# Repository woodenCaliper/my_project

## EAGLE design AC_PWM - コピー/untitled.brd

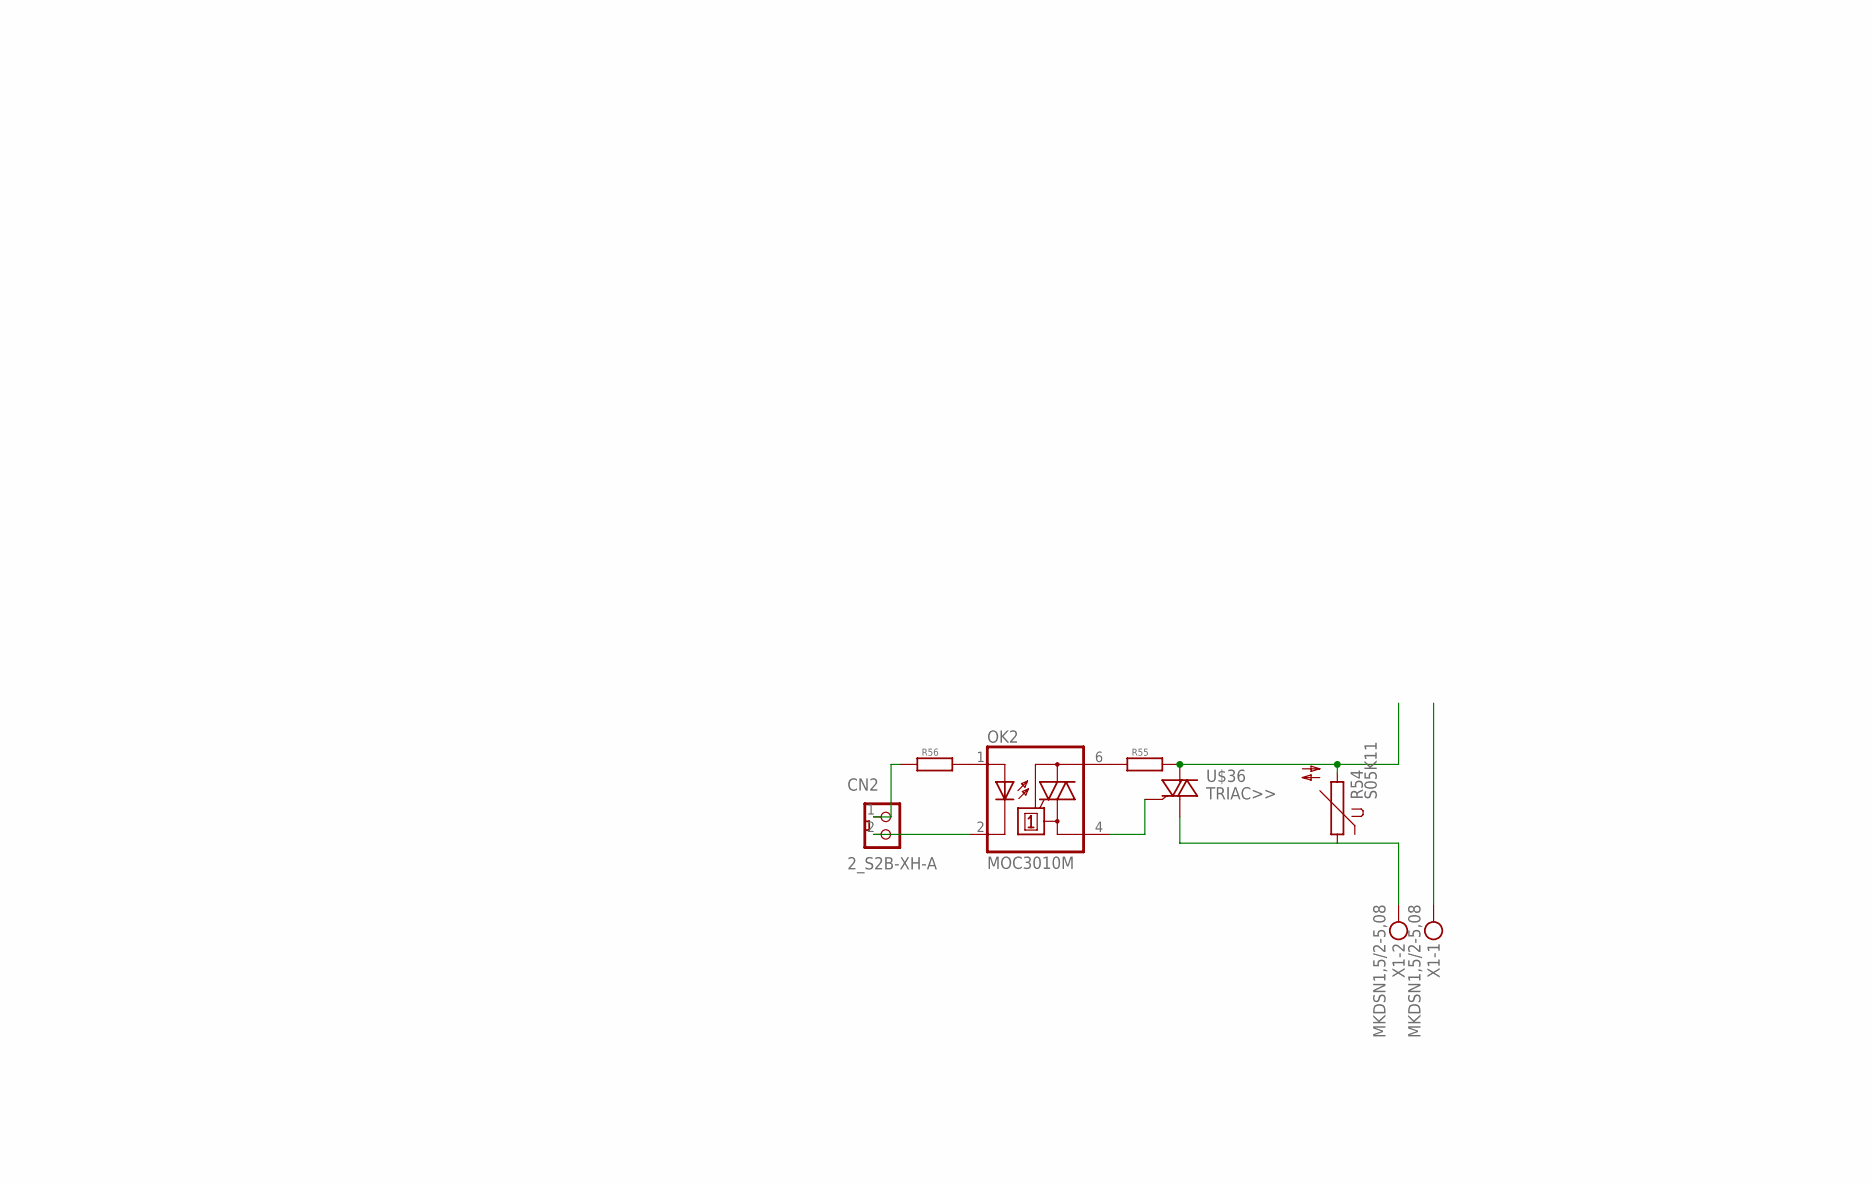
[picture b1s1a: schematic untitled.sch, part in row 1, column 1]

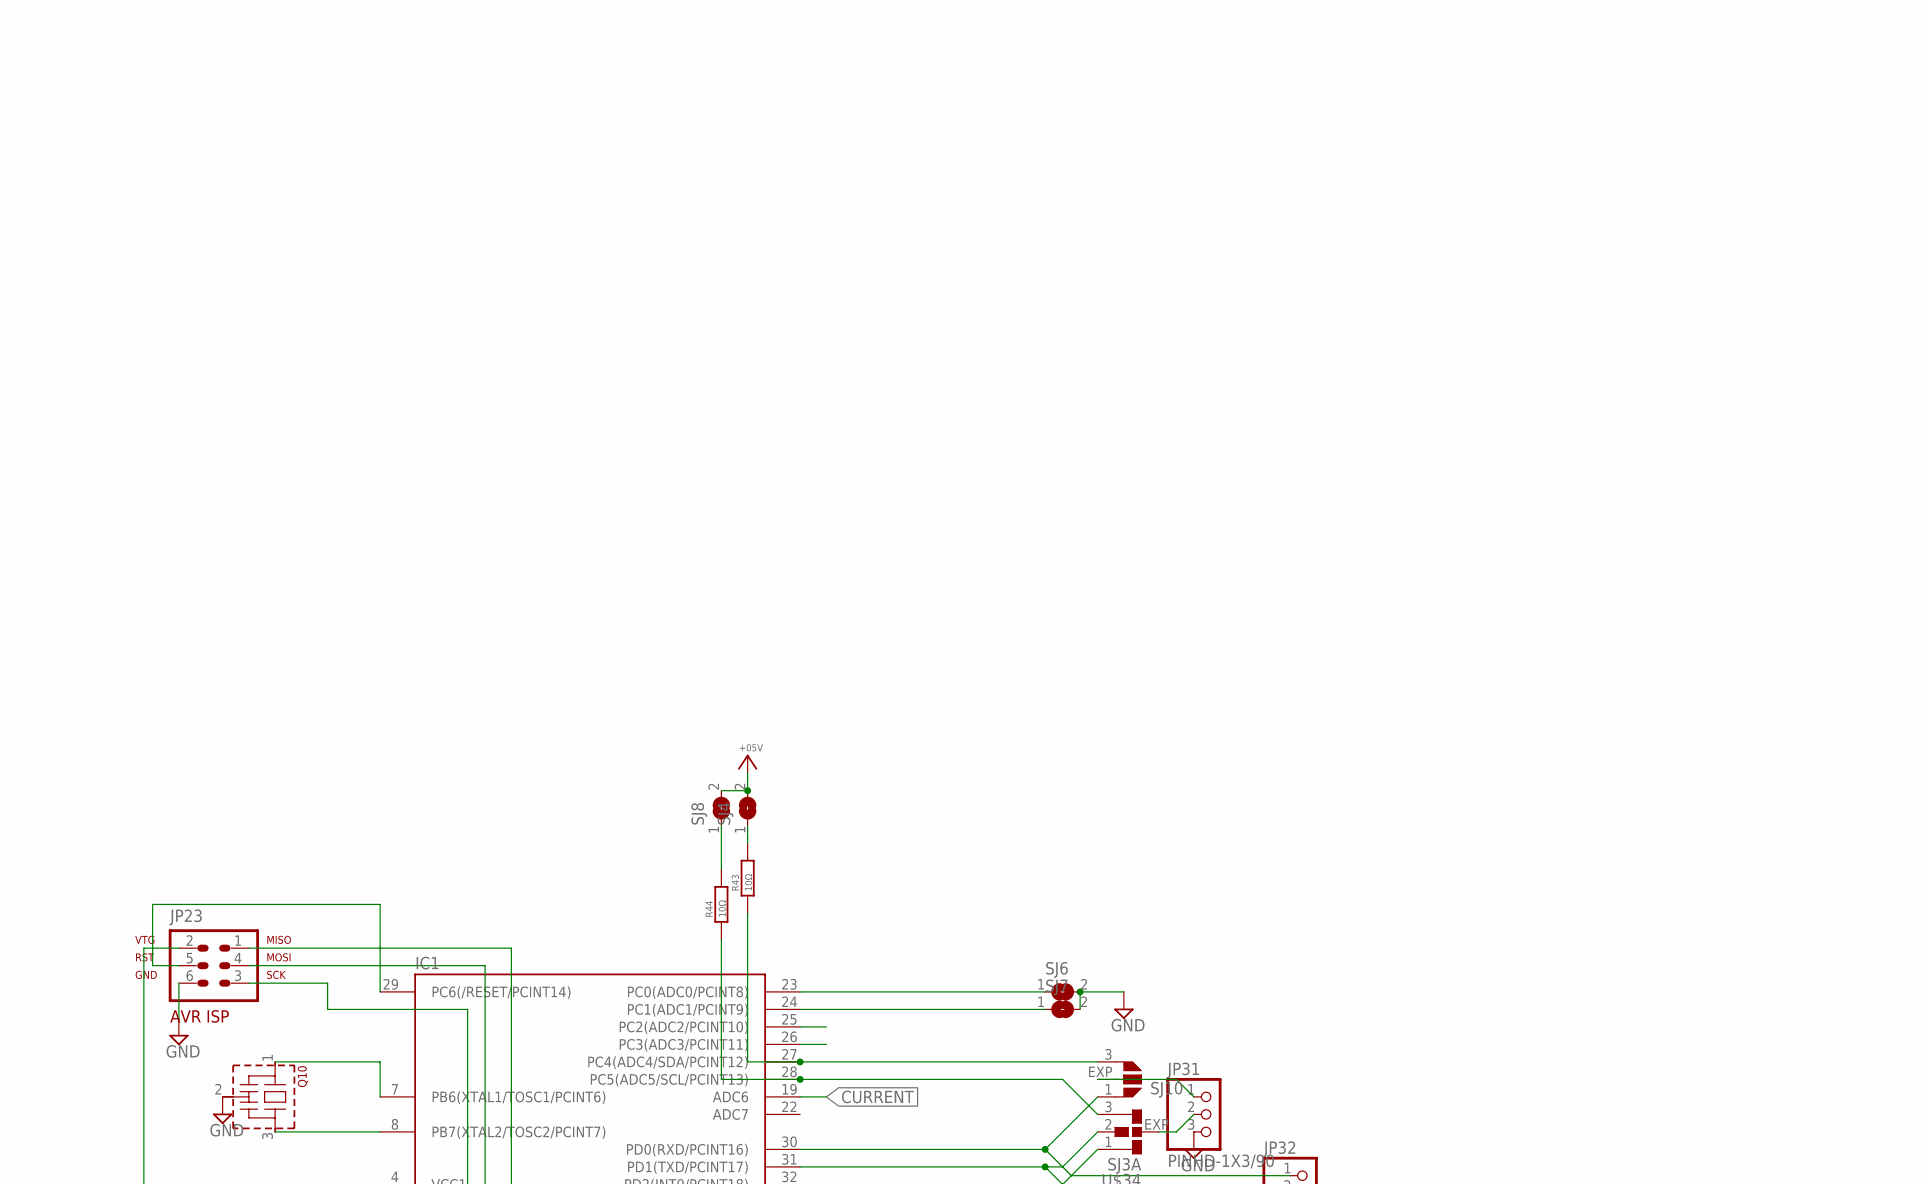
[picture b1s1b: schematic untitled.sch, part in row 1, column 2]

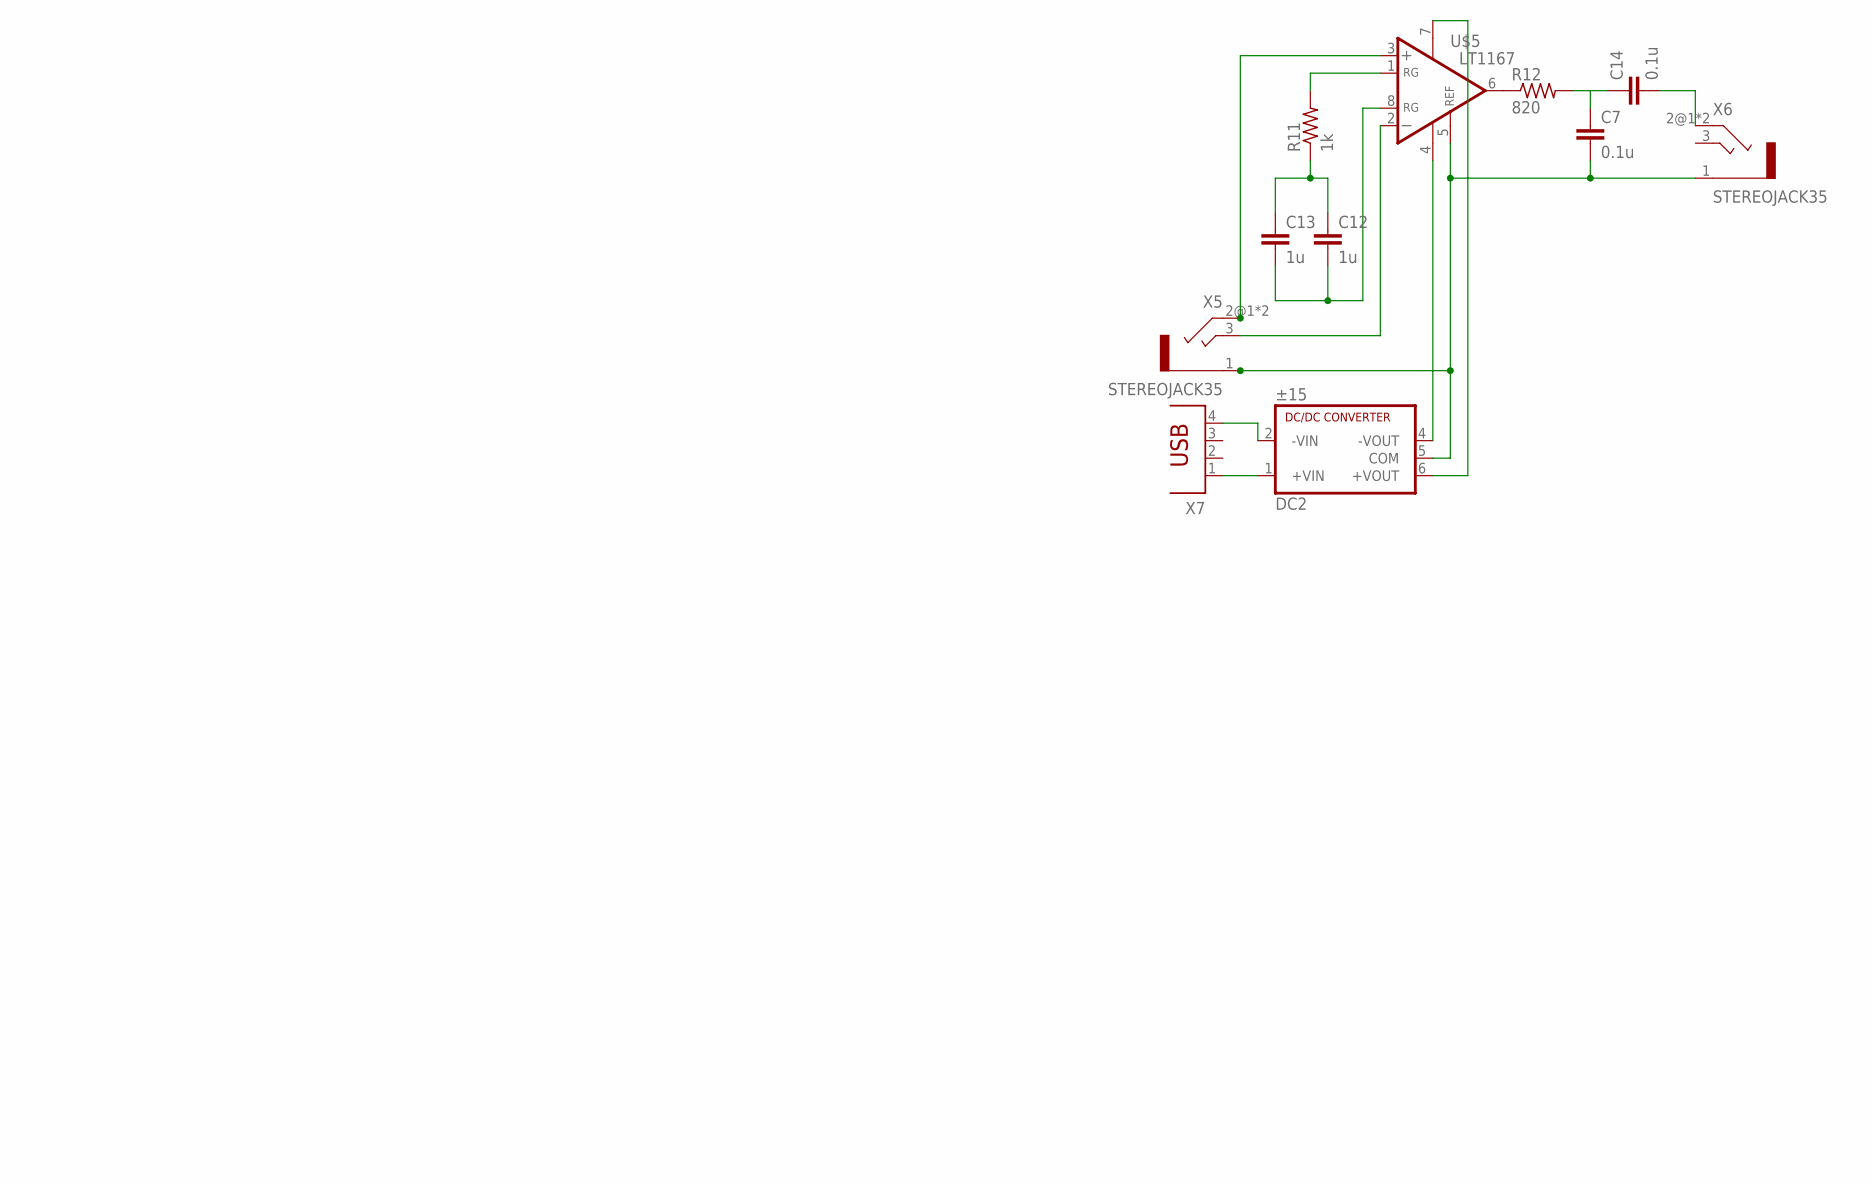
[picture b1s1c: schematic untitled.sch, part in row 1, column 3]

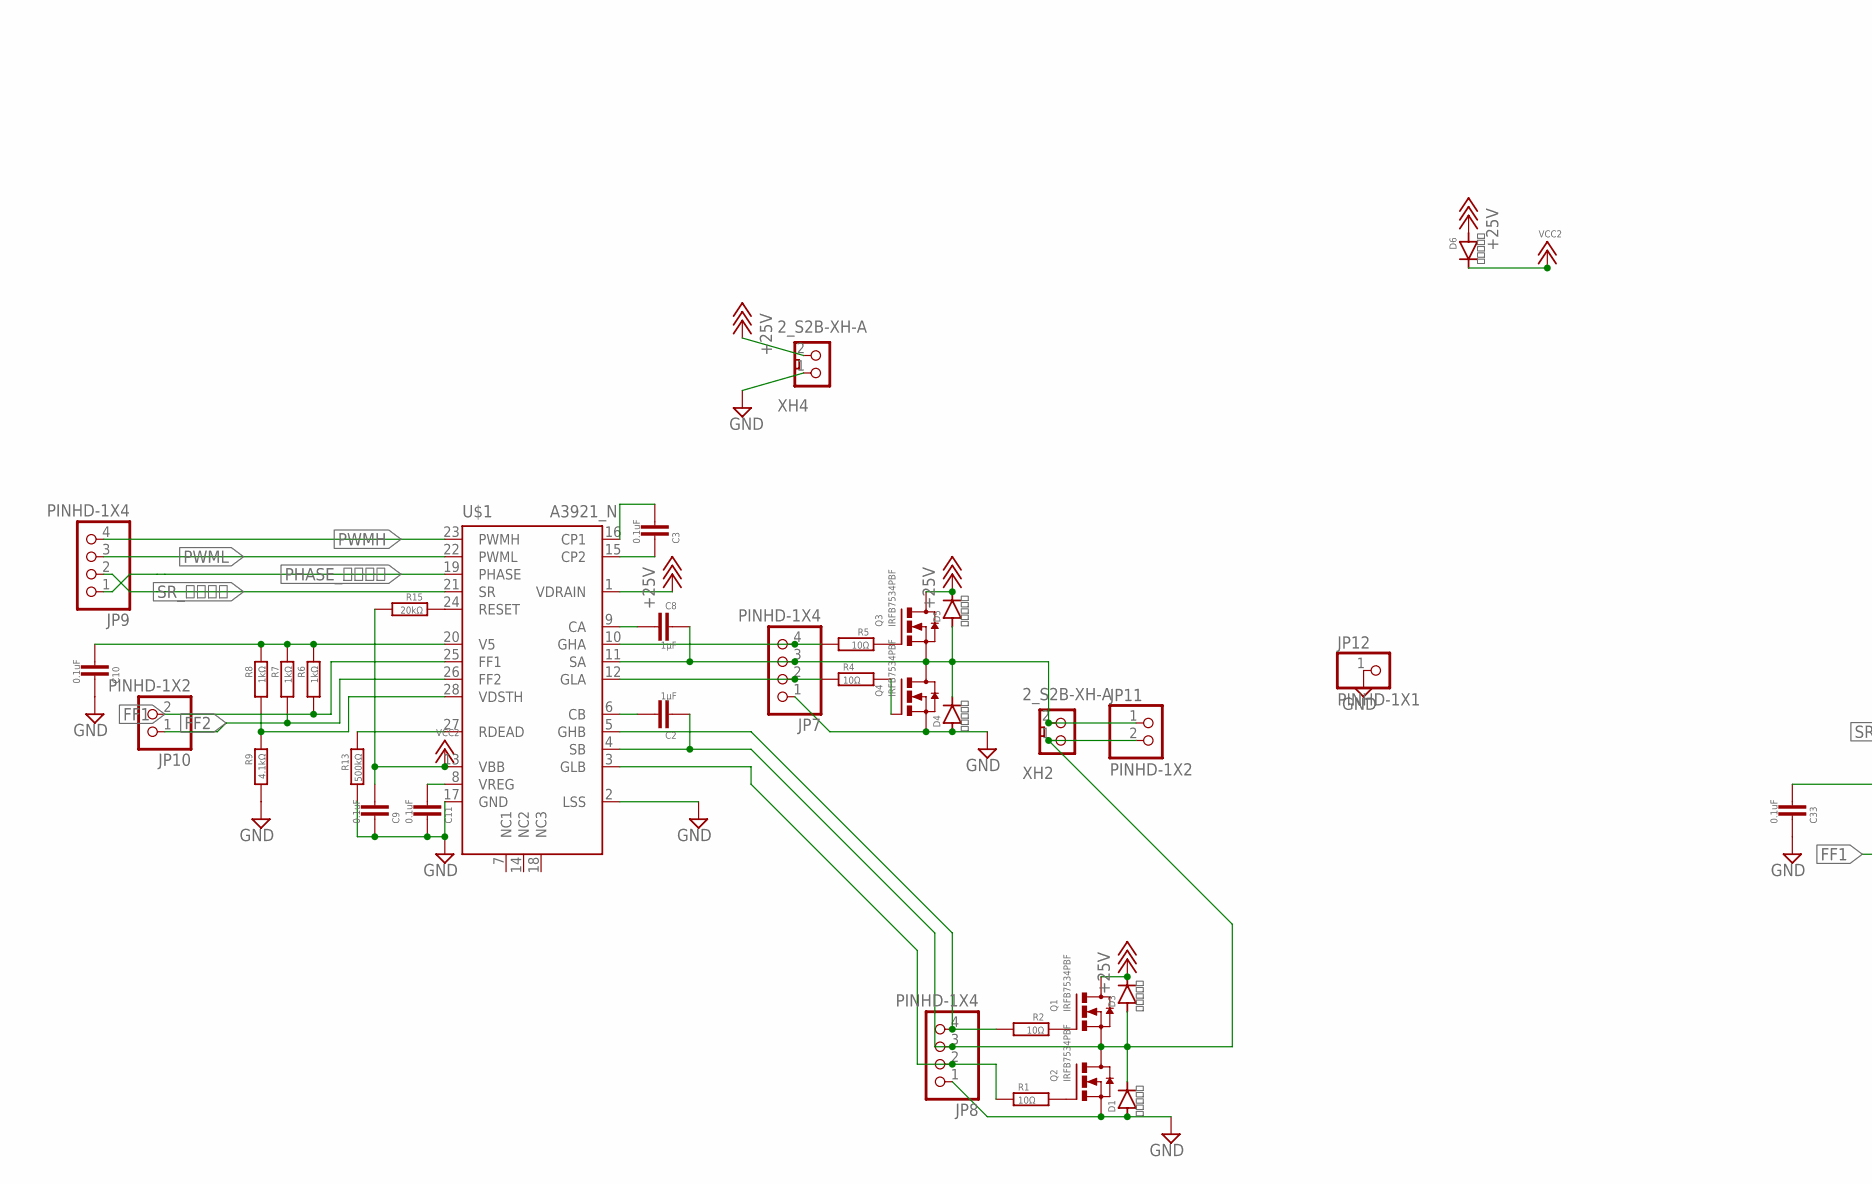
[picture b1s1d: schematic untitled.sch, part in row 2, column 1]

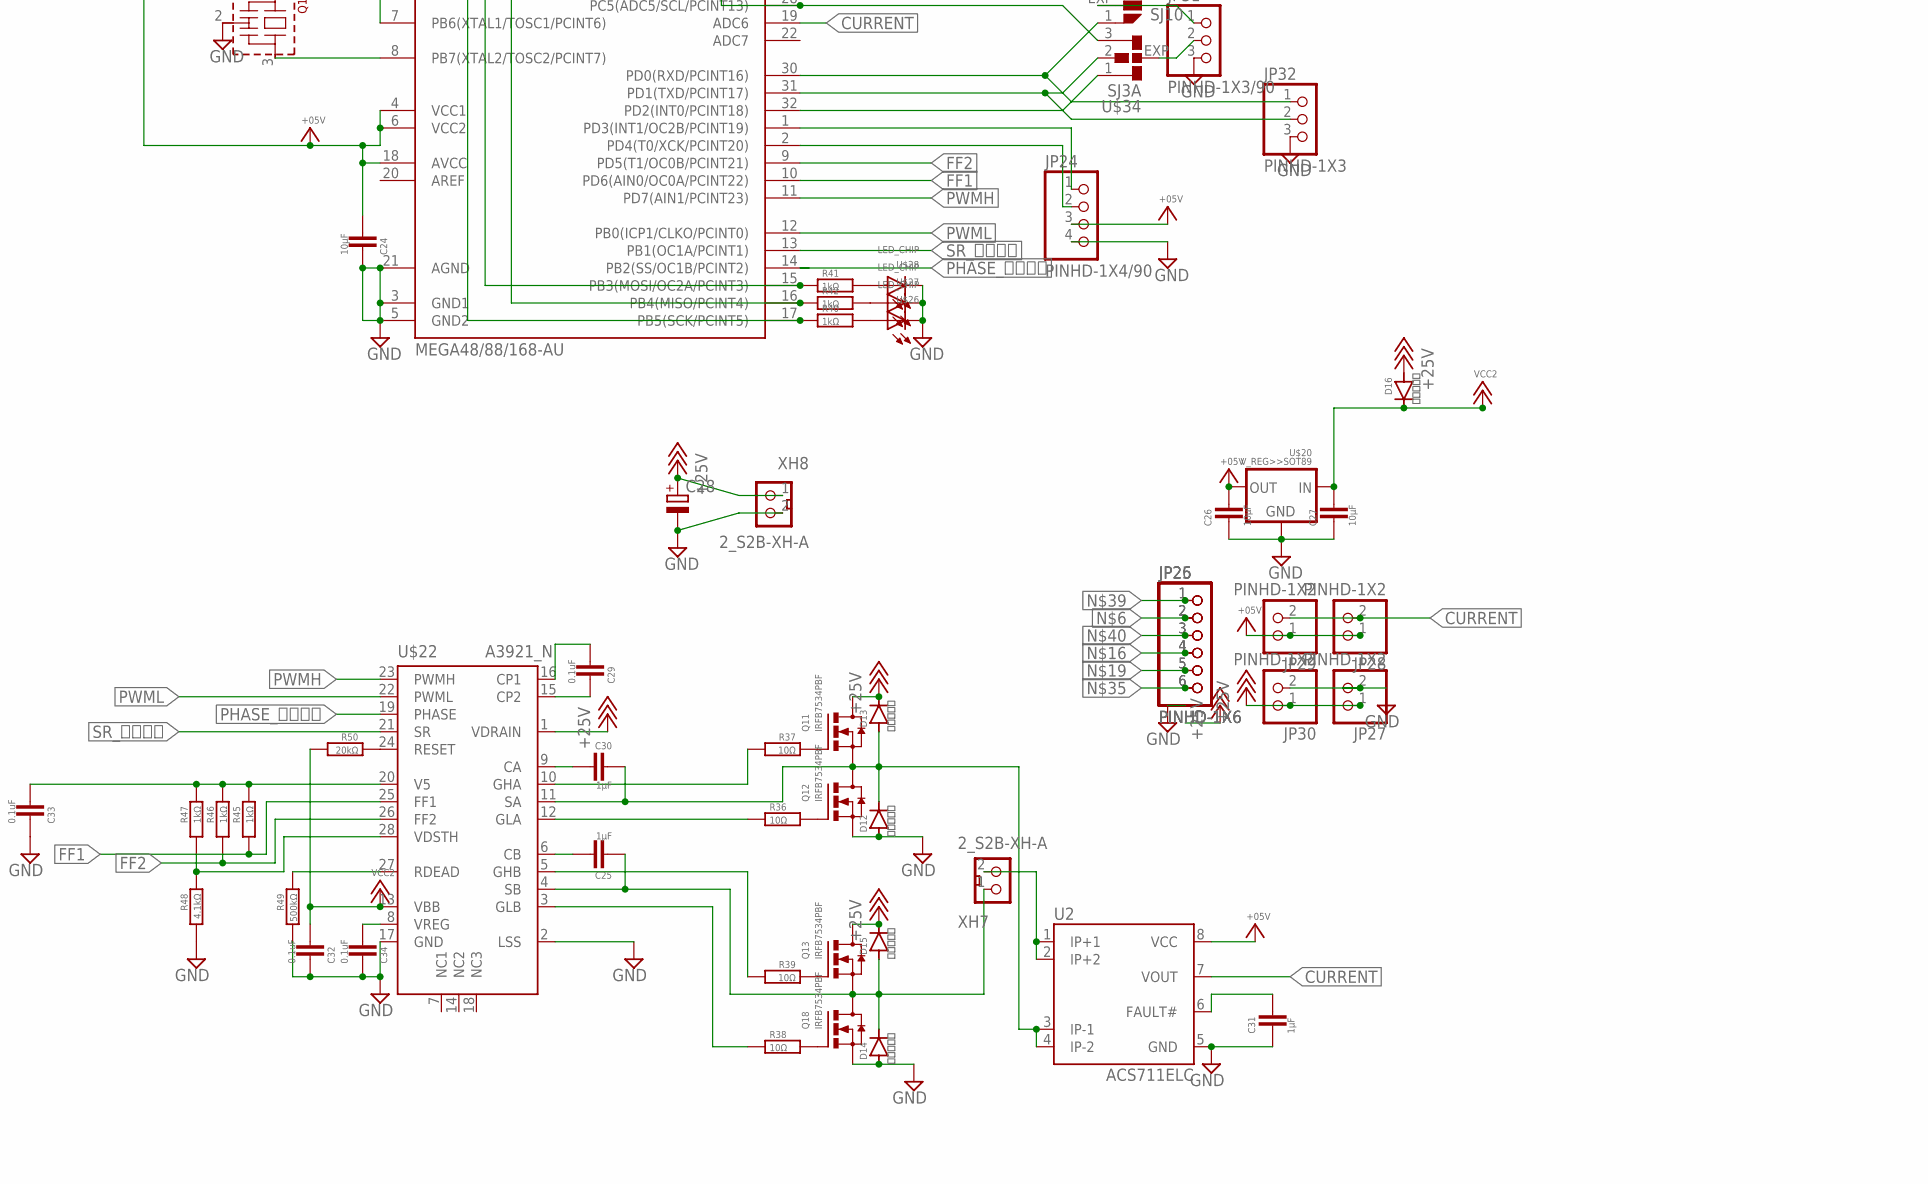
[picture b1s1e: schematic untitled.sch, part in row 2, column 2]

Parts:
C2, C8, C25, C30, C31: 1μF; 2012
C3, C9, C10, C11, C29, C32, C33, C34: 0.1uF; 2012
C7, C14: 0.1u; C050-024X044
C12, C13: 1u; C050-024X044
C24, C26, C27: 10μF; 2012
C28: CPOL-EUUD-6,3X8,8; UD-6,3X5,8_NICHICON
CN2: 2_S2B-XH-A; S2B-XH-A
D1, D3, D4, D5, D6, D12, D13, D14, D15, D16: ＭＳ１８Ｆ; MS18F
DC2: ±15; NMA
IC1: MEGA48/88/168-AU; TQFP32-08
JP7, JP8, JP9: PINHD-1X4; 1X04
JP10, JP11, JP27, JP28, JP29, JP30: PINHD-1X2; 1X02
JP12: PINHD-1X1; 1X01
JP23: AVR-ISP-6
JP24: PINHD-1X4/90; 1X04/90
JP25, JP26: PINHD-1X6; 1X06
JP31: PINHD-1X3/90; 1X03/90
JP32: PINHD-1X3; 1X03
OK2: MOC3010M; DIL06
Q1, Q2, Q3, Q4, Q11, Q12, Q13, Q18: IRFB7534PBF; TO252
Q10: CSTLS_G; CSTLS_G8
R1, R2, R4, R5, R36, R37, R38, R39, R43, R44: 10Ω; 2012
R6, R7, R8, R40, R41, R42, R45, R46, R47: 1kΩ; 2012
R9, R48: 4.1kΩ; 2012
R11: 1k; 0207/7
R12: 820; 0207/7
R13, R49: 500kΩ; 2012
R15, R50: 20kΩ; 2012
R54: S05K11
R55, R56: R-EU>>1/4W(8MM); 1/4W(8MM)
SJ4, SJ6, SJ7, SJ8: SJSS; SJ_B
SJ10: SJ2; SJ2_A
U2: ACS711ELC; SOIC8
U$1, U$22: A3921_N; TSSOP28_N
U$5: LT1167; DIL08
U$20: V_REG>>SOT89; SOT89
U$26, U$27, U$28: LED_CHIP; 2012
U$34: SJ3A; SJ3_A
U$36: TRIAC>>; TO-220_BT
X1: MKDSN1,5/2-5,08
X5, X6: STEREOJACK35
X7: PN87520
XH2, XH4, XH7, XH8: 2_S2B-XH-A; S2B-XH-A

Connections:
+5V: C24.1, C26.1, IC1.4 (VCC1), IC1.6 (VCC2), IC1.18 (AVCC), JP23.2, JP24.3, JP28.1, JP29.1, SJ4.2, SJ8.2, U2.8 (VCC), U$20.1 (OUT)
+18V: C28.+, D3.P$2 (C), D5.P$2 (C), D6.P$1 (A), D13.P$2 (C), D15.P$2 (C), D16.P$1 (A), JP27.1, JP30.1, Q1.3 (D), Q3.3 (D), Q11.3 (D), Q13.3 (D), U$1.1 (VDRAIN), U$22.1 (VDRAIN), XH4.2, XH8.1
CURRENT: IC1.19 (ADC6), JP28.2, JP29.2, U2.7 (VOUT)
FF1: IC1.10 (PD6(AIN0/OC0A/PCINT22)), JP10.2, R6.2, R45.2, U$1.25 (FF1), U$22.25 (FF1)
FF2: IC1.9 (PD5(T1/OC0B/PCINT21)), JP10.1, R7.2, R46.2, U$1.26 (FF2), U$22.26 (FF2)
GND: C9.2, C10.2, C11.2, C24.2, C26.2, C27.2, C28.-, C31.2, C32.2, C33.2, C34.2, D1.P$1 (A), D4.P$1 (A), D12.P$1 (A), D14.P$1 (A), IC1.3 (GND1), IC1.5 (GND2), IC1.21 (AGND), JP7.1, JP8.1, JP12.1, JP23.6, JP24.4, JP27.2, JP30.2, JP31.3, JP32.3, Q2.2 (S), Q4.2 (S), Q10.2 (VSS), Q12.2 (S), Q18.2 (S), R9.2, R13.2, R48.2, R49.2, SJ6.2, SJ7.2, U2.5 (GND), U$1.2 (LSS), U$1.17 (GND), U$20.2 (GND), U$20.2.1 (GND), U$22.2 (LSS), U$22.17 (GND), U$26.P$2 (C), U$27.P$2 (C), U$28.P$2 (C), XH4.1, XH8.2
unnamed: Q2.1 (G), R1.2
unnamed: Q1.1 (G), R2.1
unnamed: Q4.1 (G), R4.2
unnamed: C25.2, D14.P$2 (C), D15.P$1 (A), JP25.2, JP26.2, Q3.1 (G), Q13.2 (S), Q18.3 (D), R5.1, U$22.4 (SB), XH7.1
unnamed: C3.1, U$1.16 (CP1)
unnamed: C3.2, U$1.15 (CP2)
unnamed: C8.1, U$1.9 (CA)
unnamed: JP7.4, R5.2, U$1.10 (GHA)
unnamed: JP25.4, JP26.4, R37.2, U$22.10 (GHA)
unnamed: JP7.2, R4.1, U$1.12 (GLA)
unnamed: C2.1, U$1.6 (CB)
unnamed: C30.2, D12.P$2 (C), D13.P$1 (A), JP25.5, JP26.5, Q11.2 (S), Q12.3 (D), U2.3 (IP-1), U2.4 (IP-2), U$22.11 (SA)
unnamed: R8.2, R9.1, U$1.28 (VDSTH)
unnamed: R13.1, U$1.27 (RDEAD)
unnamed: C2.2, D1.P$2 (C), D3.P$1 (A), JP8.3, JP11.2, Q1.2 (S), Q2.3 (D), U$1.4 (SB), XH2.1
unnamed: R15.1, U$1.24 (RESET)
unnamed: C11.1, U$1.8 (VREG)
unnamed: JP8.4, R2.2, U$1.5 (GHB)
unnamed: C8.2, D4.P$2 (C), D5.P$1 (A), JP7.3, JP11.1, Q3.2 (S), Q4.3 (D), U$1.11 (SA), XH2.2
unnamed: JP8.2, R1.1, U$1.3 (GLB)
unnamed: JP25.6, JP26.6, R36.1, U$22.12 (GLA)
unnamed: JP25.1, JP26.1, R39.2, U$22.5 (GHB)
unnamed: JP25.3, JP26.3, R38.1, U$22.3 (GLB)
unnamed: C7.2, DC2.5 (COM), U$5.5 (REF), X5.1, X6.1
unnamed: U$5.2 (-IN), X5.3
unnamed: U$5.3 (+IN), X5.2@1 (2), X5.2@2 (2)
unnamed: DC2.2 (-VIN), X7.4
unnamed: DC2.1 (+VIN), X7.1
unnamed: C12.2, C13.2, U$5.8 (RG)
unnamed: C12.1, C13.1, R11.1
unnamed: R11.2, U$5.1 (RG)
unnamed: DC2.4 (-VOUT), U$5.4 (V-)
unnamed: DC2.6 (+VOUT), U$5.7 (V+)
unnamed: R12.1, U$5.6 (OUT)
unnamed: C7.1, C14.1, R12.2
unnamed: C14.2, X6.2@1 (2), X6.2@2 (2)
unnamed: IC1.7 (PB6(XTAL1/TOSC1/PCINT6)), Q10.1
unnamed: IC1.8 (PB7(XTAL2/TOSC2/PCINT7)), Q10.3
unnamed: IC1.29 (PC6(/RESET/PCINT14)), JP23.5
unnamed: IC1.17 (PB5(SCK/PCINT5)), JP23.3, R40.1
unnamed: IC1.16 (PB4(MISO/PCINT4)), JP23.1, R42.1
unnamed: IC1.15 (PB3(MOSI/OC2A/PCINT3)), JP23.4, R41.1
unnamed: Q12.1 (G), R36.2
unnamed: Q11.1 (G), R37.1
unnamed: Q18.1 (G), R38.2
unnamed: Q13.1 (G), R39.1
unnamed: R44.2, SJ8.1
unnamed: C29.1, U$22.16 (CP1)
unnamed: C29.2, U$22.15 (CP2)
unnamed: C30.1, U$22.9 (CA)
unnamed: C25.1, U$22.6 (CB)
unnamed: R47.2, R48.1, U$22.28 (VDSTH)
unnamed: R49.1, U$22.27 (RDEAD)
unnamed: C31.1, U2.6 (FAULT#)
unnamed: IC1.2 (PD4(T0/XCK/PCINT20)), JP24.2
unnamed: IC1.1 (PD3(INT1/OC2B/PCINT19)), JP24.1
unnamed: R40.2, U$26.P$1 (A)
unnamed: R42.2, U$27.P$1 (A)
unnamed: R41.2, U$28.P$1 (A)
unnamed: U2.1 (IP+1), U2.2 (IP+2), XH7.2
unnamed: IC1.23 (PC0(ADC0/PCINT8)), SJ6.1
unnamed: IC1.24 (PC1(ADC1/PCINT9)), SJ7.1
unnamed: R43.2, SJ4.1
unnamed: JP31.2, U$34.EXP
unnamed: JP31.1, SJ10.EXP (2)
unnamed: IC1.32 (PD2(INT0/PCINT18)), U$34.1
unnamed: IC1.31 (PD1(TXD/PCINT17)), JP32.2, U$34.2
unnamed: IC1.30 (PD0(RXD/PCINT16)), JP32.1, SJ10.1
unnamed: IC1.28 (PC5(ADC5/SCL/PCINT13)), R44.1, U$34.3
unnamed: IC1.27 (PC4(ADC4/SDA/PCINT12)), R43.1, SJ10.3
unnamed: R50.1, U$22.24 (RESET)
unnamed: C34.1, U$22.8 (VREG)
unnamed: OK2.6 (A2), R55.1
unnamed: R54.2, R55.2, U$36.2 (A2)
unnamed: OK2.4 (A1), U$36.1 (G)
unnamed: R54.1, U$36.3 (A1), X1.2
unnamed: OK2.1 (A), R56.2
unnamed: CN2.1, R56.1
unnamed: CN2.2, OK2.2 (C)
PHASE_正転逆転: IC1.14 (PB2(SS/OC1B/PCINT2)), JP9.1, U$1.19 (PHASE), U$22.19 (PHASE)
PWMH: IC1.11 (PD7(AIN1/PCINT23)), JP9.4, U$1.23 (PWMH), U$22.23 (PWMH)
PWML: IC1.12 (PB0(ICP1/CLKO/PCINT0)), JP9.3, U$1.22 (PWML), U$22.22 (PWML)
SR_ブレーキ: IC1.13 (PB1(OC1A/PCINT1)), JP9.2, U$1.21 (SR), U$22.21 (SR)
V1: C10.1, R6.1, R7.1, R8.1, U$1.20 (V5)
V3: C33.1, R45.1, R46.1, R47.1, U$22.20 (V5)
VCC2: C9.1, C27.1, C32.1, D6.P$2 (C), D16.P$2 (C), R15.2, R50.2, U$1.13 (VBB), U$20.3 (IN), U$22.13 (VBB)

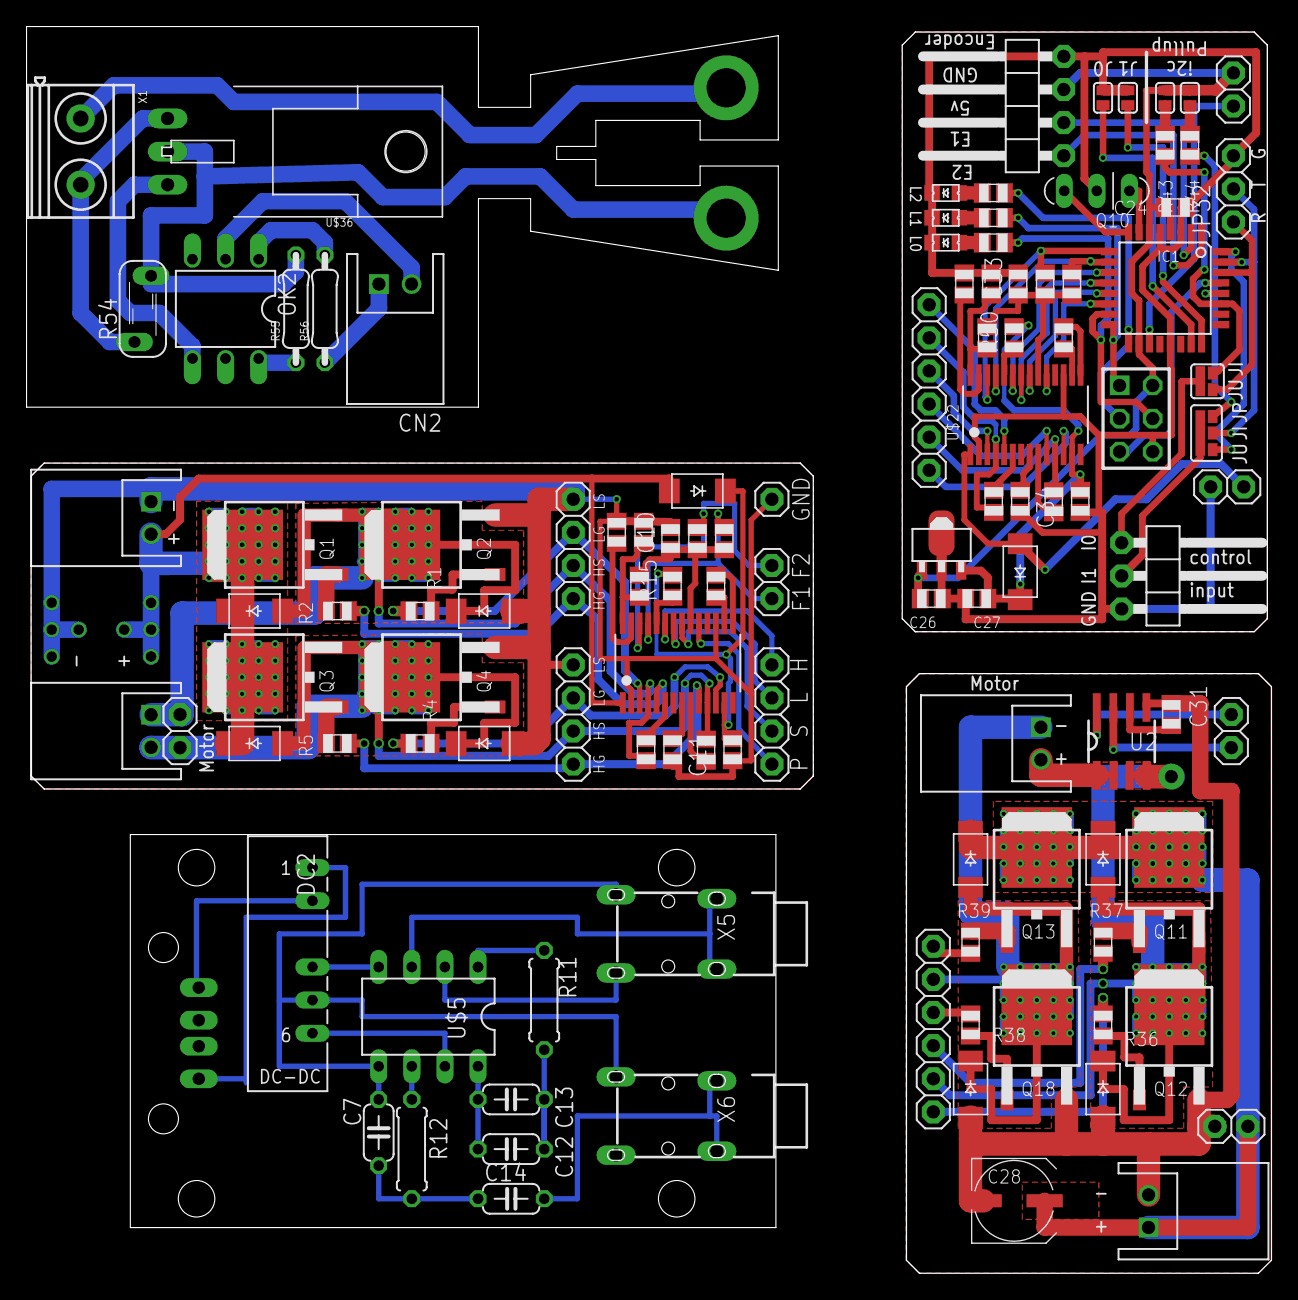
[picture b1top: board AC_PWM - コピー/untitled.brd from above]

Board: 2 copper layers, 95.5 x 95.6 mm, 113 parts (1 on the bottom side), 92 nets.

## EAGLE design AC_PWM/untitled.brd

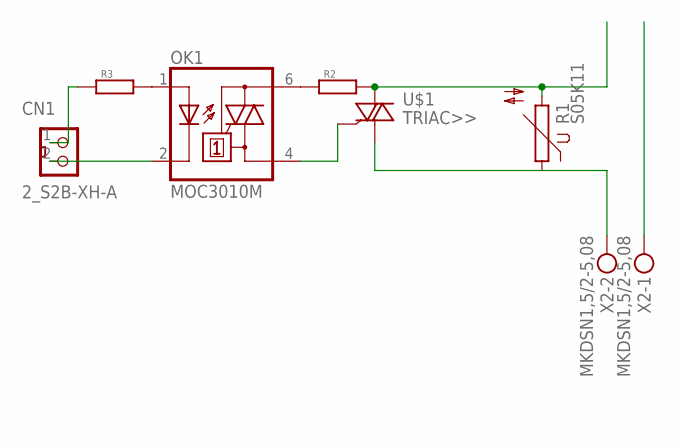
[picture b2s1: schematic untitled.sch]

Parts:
CN1: 2_S2B-XH-A; S2B-XH-A
OK1: MOC3010M; DIL06
R1: S05K11
R2, R3: R-EU>>1/4W(8MM); 1/4W(8MM)
U$1: TRIAC>>; TO-220_BT
X2: MKDSN1,5/2-5,08

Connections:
unnamed: OK1.6 (A2), R2.1
unnamed: R1.2, R2.2, U$1.2 (A2)
unnamed: OK1.4 (A1), U$1.1 (G)
unnamed: R1.1, U$1.3 (A1), X2.2
unnamed: CN1.2, OK1.2 (C)
unnamed: OK1.1 (A), R3.2
unnamed: CN1.1, R3.1

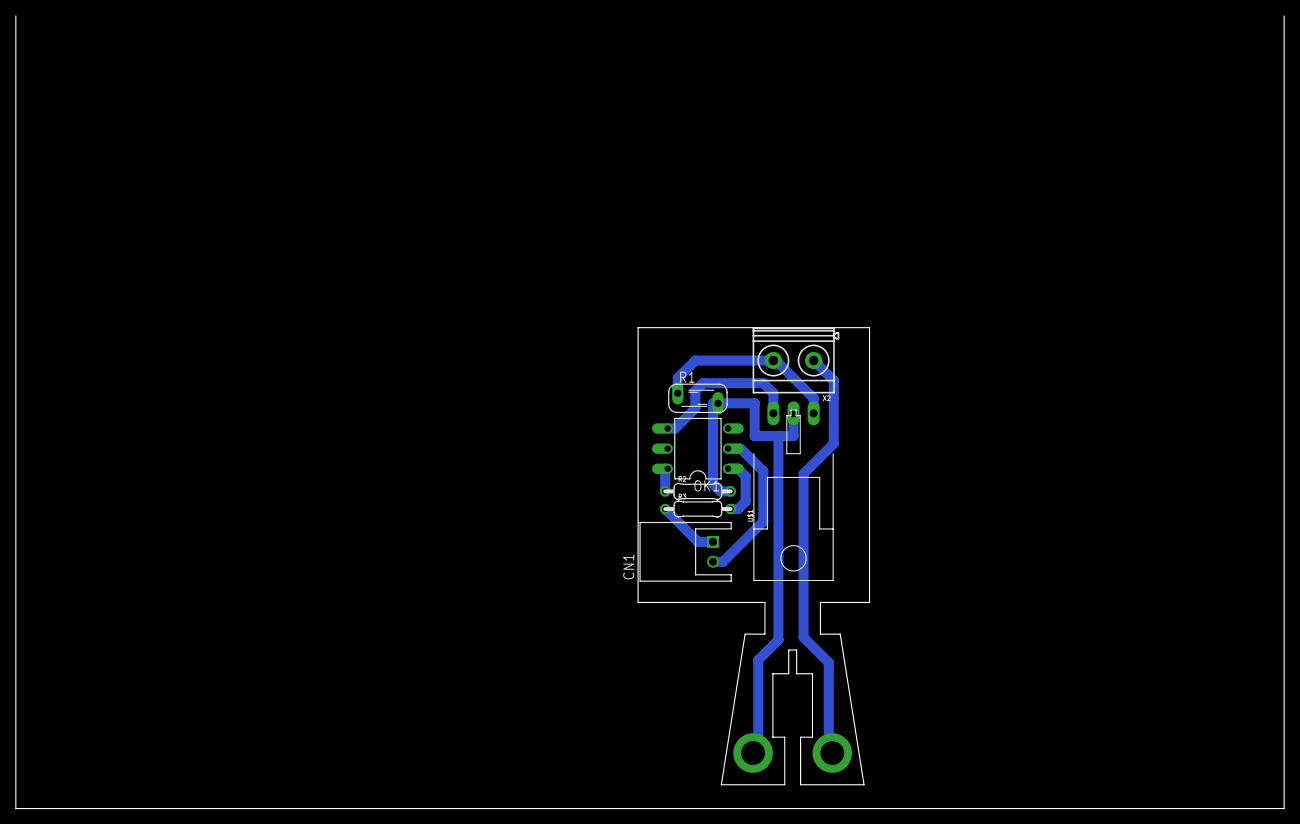
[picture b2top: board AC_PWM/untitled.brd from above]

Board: 2 copper layers, 29.2 x 57.7 mm, 7 parts (0 on the bottom side), 7 nets.

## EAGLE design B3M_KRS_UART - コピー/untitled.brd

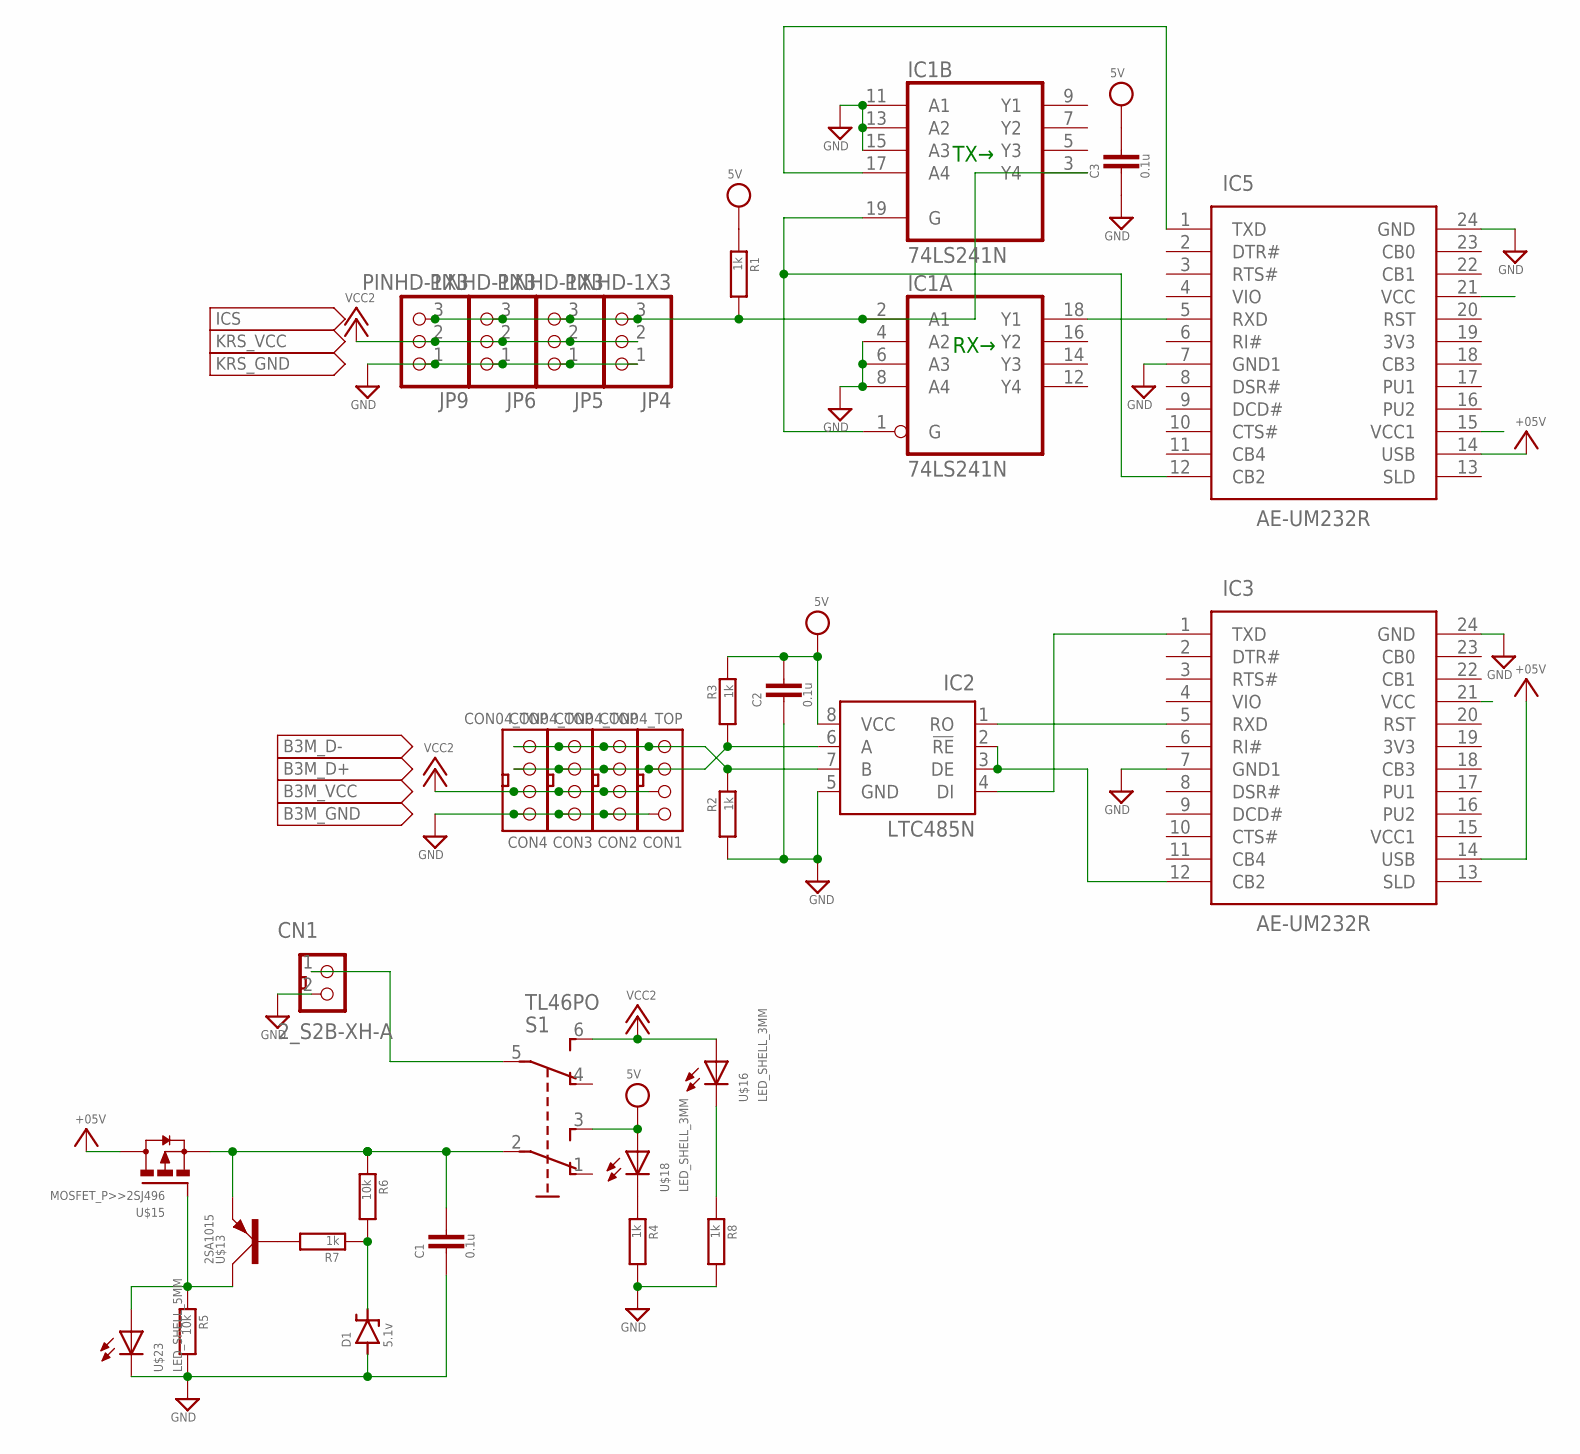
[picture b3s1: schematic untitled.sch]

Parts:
C1, C2, C3: 0.1u; C050-024X044
CN1: 2_S2B-XH-A; S2B-XH-A
CON1, CON2, CON3, CON4: CON04_TOP; TOP_CON4
D1: 5.1v; ZDIO-5
IC1: 74LS241N; DIL20
IC2: LTC485N; DIL08
IC3, IC5: AE-UM232R
JP4, JP5, JP6, JP9: PINHD-1X3; 1X03
R1, R2, R3, R4, R7, R8: 1k; 1/4W(8MM)
R5, R6: 10k; 1/4W(8MM)
S1: TL46PO; TL4XPO
U$13: 2SA1015; TO-92
U$15: MOSFET_P>>2SJ496; TO-92
U$16, U$18: LED_SHELL_3MM; 3MM
U$23: LED_SHELL_5MM; 5MM

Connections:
+5V: IC3.14 (USB), IC5.14 (USB), U$15.2 (D)
GND: C1.2, C2.2, C3.2, CN1.2, CON1.P$1 (1), CON2.P$1 (1), CON3.P$1 (1), CON4.P$1 (1), D1.A, IC1.4 (A2), IC1.6 (A3), IC1.8 (A4), IC1.10 (GND), IC1.11 (A1), IC1.13 (A2), IC1.15 (A3), IC2.5 (GND), IC3.7 (GND1), IC3.24 (GND), IC5.7 (GND1), IC5.24 (GND), JP4.1, JP5.1, JP6.1, JP9.1, R2.2, R4.2, R5.2, R8.2, U$23.P$2 (C)
ICS: IC1.2 (A1), IC1.3 (Y4), JP4.3, JP5.3, JP6.3, JP9.3, R1.2
unnamed: IC1.18 (Y1), IC5.5 (RXD)
unnamed: IC2.4 (DI), IC3.1 (TXD)
unnamed: IC1.1 (G), IC1.19 (G), IC5.12 (CB2)
unnamed: CN1.1, S1.5 (P1)
unnamed: C1.1, R6.1, S1.2, U$13.1 (E), U$15.1 (S)
unnamed: R5.1, U$13.2 (C), U$15.3 (G), U$23.P$1 (A)
unnamed: D1.C, R6.2, R7.1
unnamed: R7.2, U$13.3 (B)
unnamed: R8.1, U$16.P$2 (C)
unnamed: R4.1, U$18.P$2 (C)
unnamed: CON1.P$4 (4), CON2.P$4 (4), CON3.P$4 (4), CON4.P$4 (4), IC2.7 (B), R2.1
unnamed: CON1.P$3 (3), CON2.P$3 (3), CON3.P$3 (3), CON4.P$3 (3), IC2.6 (A), R3.2
RXD: IC2.1 (RO), IC3.5 (RXD)
TXD: IC1.17 (A4), IC5.1 (TXD)
TXDEN: IC2.2 (!RE), IC2.3 (DE), IC3.12 (CB2)
VCC: C2.1, C3.1, IC1.20 (VCC), IC2.8 (VCC), R1.1, R3.1, S1.3 (S), U$18.P$1 (A)
VCC1: IC3.15 (VCC1)
VCC2: CON1.P$2 (2), CON2.P$2 (2), CON3.P$2 (2), CON4.P$2 (2), JP4.2, JP5.2, JP6.2, JP9.2, S1.6 (S1), U$16.P$1 (A)

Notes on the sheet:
RX→
TX→
